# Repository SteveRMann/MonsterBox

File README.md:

# MonsterBox
This project is a monster in a box for Halloween.
It describes building the crate from wood salvaged from palletts,
and the code to randomly open the box.

The motors were from power drills.  The main door motor drives an offset disc, like a cam, that 
bumps the door open anot an inch.  By controlling the door, we can open for a peek or bounce the lid to get attention.

An ultrasonic fog transducer from Amazon is also inside the box to add fog effects.

## Crate
Contains images and ideas for the crate construction

## eggDrop
This is the code that operates a servo to drop an egg.
EggDrop is separate from the monster box, but basically it drops a plastic egg on command.

## Fan
Contains the schematic files for the fan and LED MOSFET controller.

## HBridgeTest
Code to test the H-Bridges

## Lid
Contains the Arduino source code for the lid mechanism.

## Notes
Just contains random notes used while making the box

## Sounds
Contains the sound files and editing information. It also contains the DFPlayer notes.

## servoSweep
Code to sweep the servo 0-180 degrees.

## servoManualSweep
Code used to calibrate the PWM endpoints for servo.h

## tail
Code to make the dragon's tail sweep back and forth

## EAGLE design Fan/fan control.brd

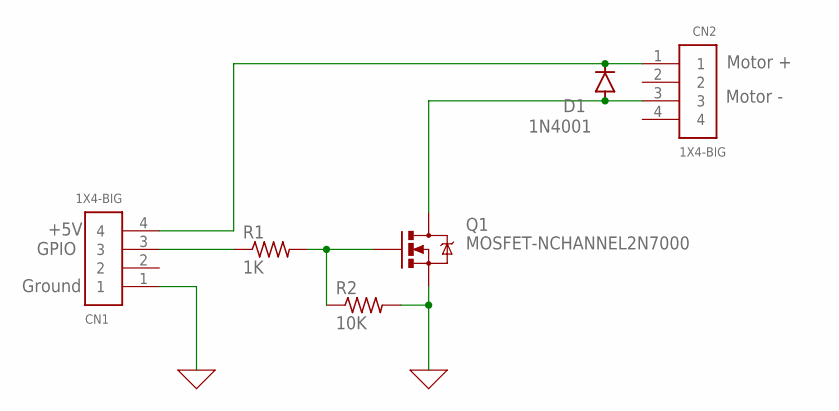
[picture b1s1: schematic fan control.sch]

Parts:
CN1, CN2: 1X4-BIG; 1X04-BIG
D1: 1N4001; DO-41
Q1: MOSFET-NCHANNEL2N7000; TO-92
R1: 1K; 0207/10
R2: 10K; 0207/10

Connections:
0: CN1.1, Q1.1 (S), R2.2
unnamed: CN1.4, CN2.1, D1.C
unnamed: Q1.2 (G), R1.2, R2.1
unnamed: CN1.3, R1.1
unnamed: CN2.3, D1.A, Q1.3 (D)

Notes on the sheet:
Motor +
Motor -
+5V
GPIO
Ground

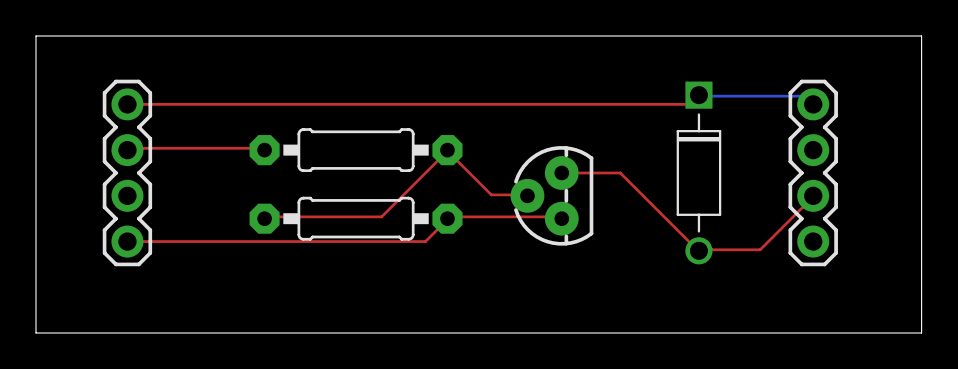
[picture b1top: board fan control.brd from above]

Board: 2 copper layers, 49.2 x 16.5 mm, 6 parts (0 on the bottom side), 5 nets.

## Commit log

2021-08-21 Initial upload
2021-09-05 Add files via upload
    Renamed from motorControl-lid
2021-09-12 New version of tail.ino
2021-09-12 Added HBridge Test
2021-09-16 Added second servo
2021-09-18 Fine-tune the timing.
